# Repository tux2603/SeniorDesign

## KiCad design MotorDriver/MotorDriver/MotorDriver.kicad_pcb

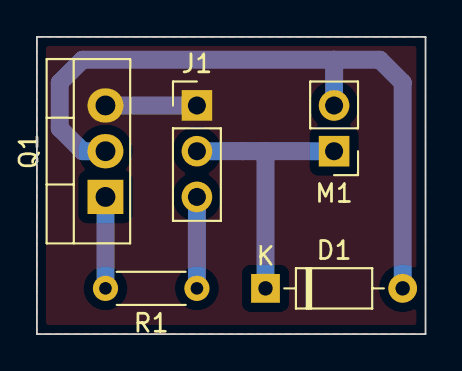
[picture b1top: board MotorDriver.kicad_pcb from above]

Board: 2 copper layers, 21.6 x 16.5 mm, 5 parts (0 on the bottom side), 5 nets.

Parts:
D1: 1N4148; D_DO-35_SOD27_P7.62mm_Horizontal
J1: Ctrl; PinHeader_1x03_P2.54mm_Vertical
M1: Pump; PinHeader_1x02_P2.54mm_Vertical
Q1: IRF540N; TO-220-3_Vertical
R1: 10k; R_Axial_DIN0204_L3.6mm_D1.6mm_P5.08mm_Horizontal

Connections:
unnamed: D1.1 (K), J1.2, M1.1 (+)
unnamed: D1.2 (A), M1.2 (-), Q1.2 (D)
unnamed: Q1.1 (G), R1.2
unnamed: J1.1, Q1.3 (S)
unnamed: J1.3, R1.1

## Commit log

2022-01-11 Update GroupMinutes.txt
    1-11
2022-01-11 Move minutes to their own folder
2022-01-11 Update MarkMinutes.txt
    1-11
2022-01-13 Add minutes for 1/11 and 1/13
2022-01-18 Updated OwenMinutes for 1/18
2022-01-20 Updated OwenMinutes.md
2022-01-27 Rename MarkMinutes.txt to MarkMinutes.md
2022-01-27 Added minutes for 1/27
2022-01-28 Create AhmedMinutes
2022-01-28 Update AhmedMinutes
2022-01-28 Update AhmedMinutes
    Thursday/01/27/2022
2022-01-28 Update AhmedMinutes
    01/27/2022- Thursday
2022-02-10 minutes for online meeting
2022-02-10 Add minutes for 2/10
2022-02-17 added inital customer page and stlesheet.css, fixed a typo on adminpage
2022-02-26 Owen Minutes Feb 24
2022-02-26 Prep line following for integration
2022-02-26 Main parts of the page are set up
2022-02-26 Basic implementation of drink queue Customers can add drinks to the queue Admin can view and clear the queue
2022-02-27 Get style sheet working with flask
2022-03-09 test
2022-03-09 test 2
2022-03-10 Add files via upload
    Design Files for 3D Print
2022-03-10 Updated Design Files in Correct units
2022-03-10 Design files final
    Clearance change. Original Import of the pump resulted in a unit change which wasn't detected until Ryan mentioned it. MVP Ryan.
2022-03-10 Owen Minutes 3/10
2022-03-31 Add motor test script
2022-04-07 Add motor control to line following
2022-04-07 Move pca9685 library to line following
2022-04-07 Fix line following calibration
2022-04-07 Owen Minutes 4/7
2022-04-12 Design camera mounting bracket
2022-04-16 Fix line following thresholds
2022-04-16 Owen Minutes 4/14
2022-04-16 Driver circuit for pump
2022-04-21 Try to open another camera if /dev/video0 isn't available
2022-04-21 Try that again
2022-04-21 Fix motor directionrs
2022-04-21 Add a sleep so it doesn't spam the console
2022-04-21 Much changes, hopefully iy should be happy now
2022-04-21 oops lol
2022-04-21 Fix turning directions
2022-04-21 Modify thresholds
2022-04-23 Update for missing minutes
2022-04-23 Forgot a check
